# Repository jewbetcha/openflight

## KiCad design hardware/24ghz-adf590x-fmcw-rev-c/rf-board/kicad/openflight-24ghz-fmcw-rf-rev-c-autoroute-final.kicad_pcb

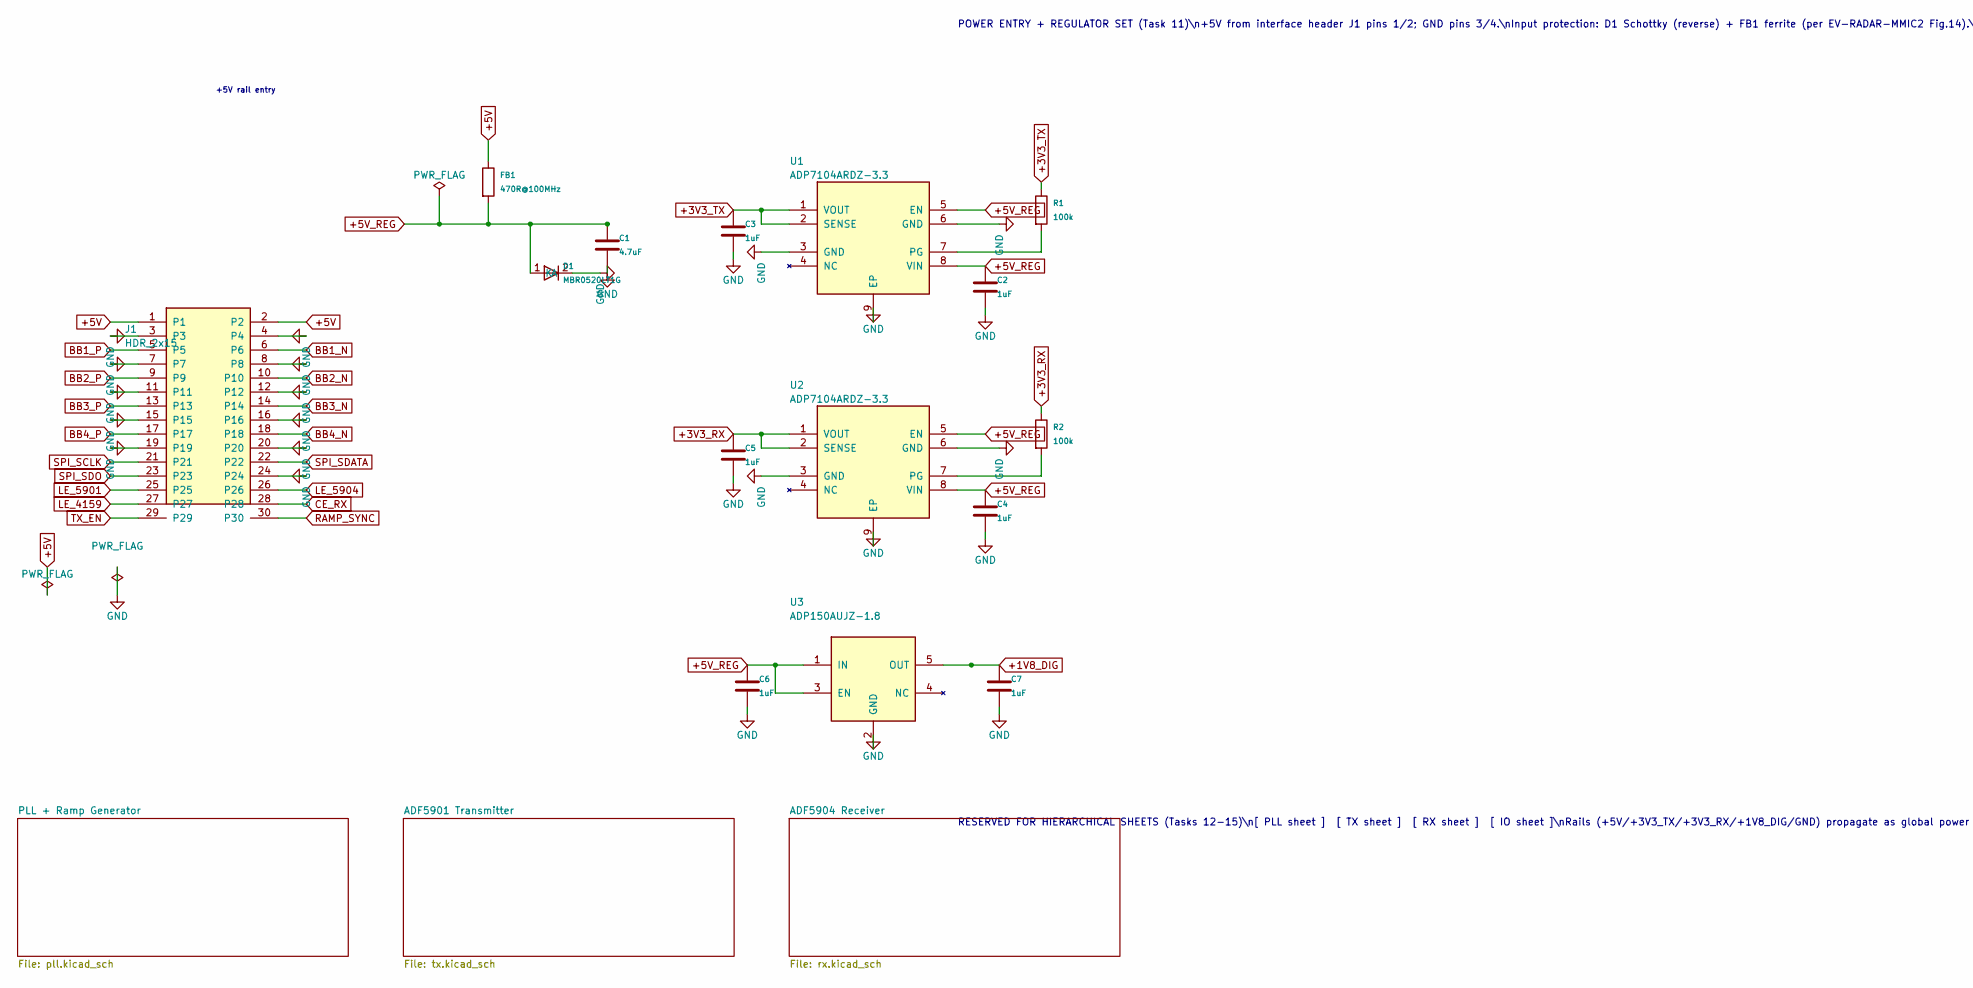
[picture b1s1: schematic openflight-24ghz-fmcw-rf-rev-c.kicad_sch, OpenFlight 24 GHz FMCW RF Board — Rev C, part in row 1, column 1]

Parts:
C1: 4.7uF; C_0603_1608Metric
C2, C3, C4, C5, C6, C7: 1uF; C_0603_1608Metric
D1: MBR0520LT1G; D_SOD-123; MPN MBR0520LT1G
FB1: 470R@100MHz; L_0603_1608Metric; MPN 742792642
J1: HDR_2x15; HDR_2x15_1.27MM_SMD; MPN FTSH-115-01-L-DV-K
R1, R2: 100k; R_0402_1005Metric
U1, U2: ADP7104ARDZ-3.3; ADP7104_SOIC8_EP; MPN ADP7104ARDZ-3.3
U3: ADP150AUJZ-1.8; ADP150_TSOT23_5; MPN ADP150AUJZ-1.8

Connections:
+1V8_DIG: C7.1, U3.5 (OUT); also elsewhere on the board
+3V3_RX: C5.1, R2.1, U2.1 (VOUT), U2.2 (SENSE); also elsewhere on the board
+3V3_TX: C3.1, R1.1, U1.1 (VOUT), U1.2 (SENSE); also elsewhere on the board
+5V: FB1.1, J1.1, J1.2; also elsewhere on the board
+5V_REG: C1.1, C2.1, C4.1, C6.1, D1.1 (K), FB1.2, U1.5 (EN), U1.8 (VIN), U2.5 (EN), U2.8 (VIN), U3.1 (IN), U3.3 (EN)
CE_RX: J1.28; also elsewhere on the board
LE_4159: J1.27; also elsewhere on the board
LE_5901: J1.25; also elsewhere on the board
LE_5904: J1.26; also elsewhere on the board
unnamed: R1.2, U1.7 (PG)
unnamed: R2.2, U2.7 (PG)
RAMP_SYNC: J1.30; also elsewhere on the board
SPI_SCLK: J1.21; also elsewhere on the board
SPI_SDATA: J1.22; also elsewhere on the board
SPI_SDO: J1.23; also elsewhere on the board
TX_EN: J1.29; also elsewhere on the board

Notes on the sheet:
POWER ENTRY + REGULATOR SET (Task 11)\n+5V from interface header J1 pins 1/2; GND pins 3/4.\nInput protection: D1 Schottky (reverse) + FB1 ferrite (per EV-RADAR-MMIC2 Fig.14).\nU1 ADP7104-3.3 -> +3V3_TX (ADF5901). U2 ADP7104-3.3 -> +3V3_RX (ADF5904 + ADF4159 analog).\nU3 ADP150-1.8 -> +1V8_DIG (ADF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
RESERVED FOR HIERARCHICAL SHEETS (Tasks 12-15)\n[ PLL sheet ] [ TX sheet ] [ RX sheet ] [ IO sheet ]\nRails (+5V/+3V3_TX/+3V3_RX/+1V8_DIG/GND) propagate as global power symbols;\nsignals cross via hierarchical pins added by those tasks.
+5V rail entry

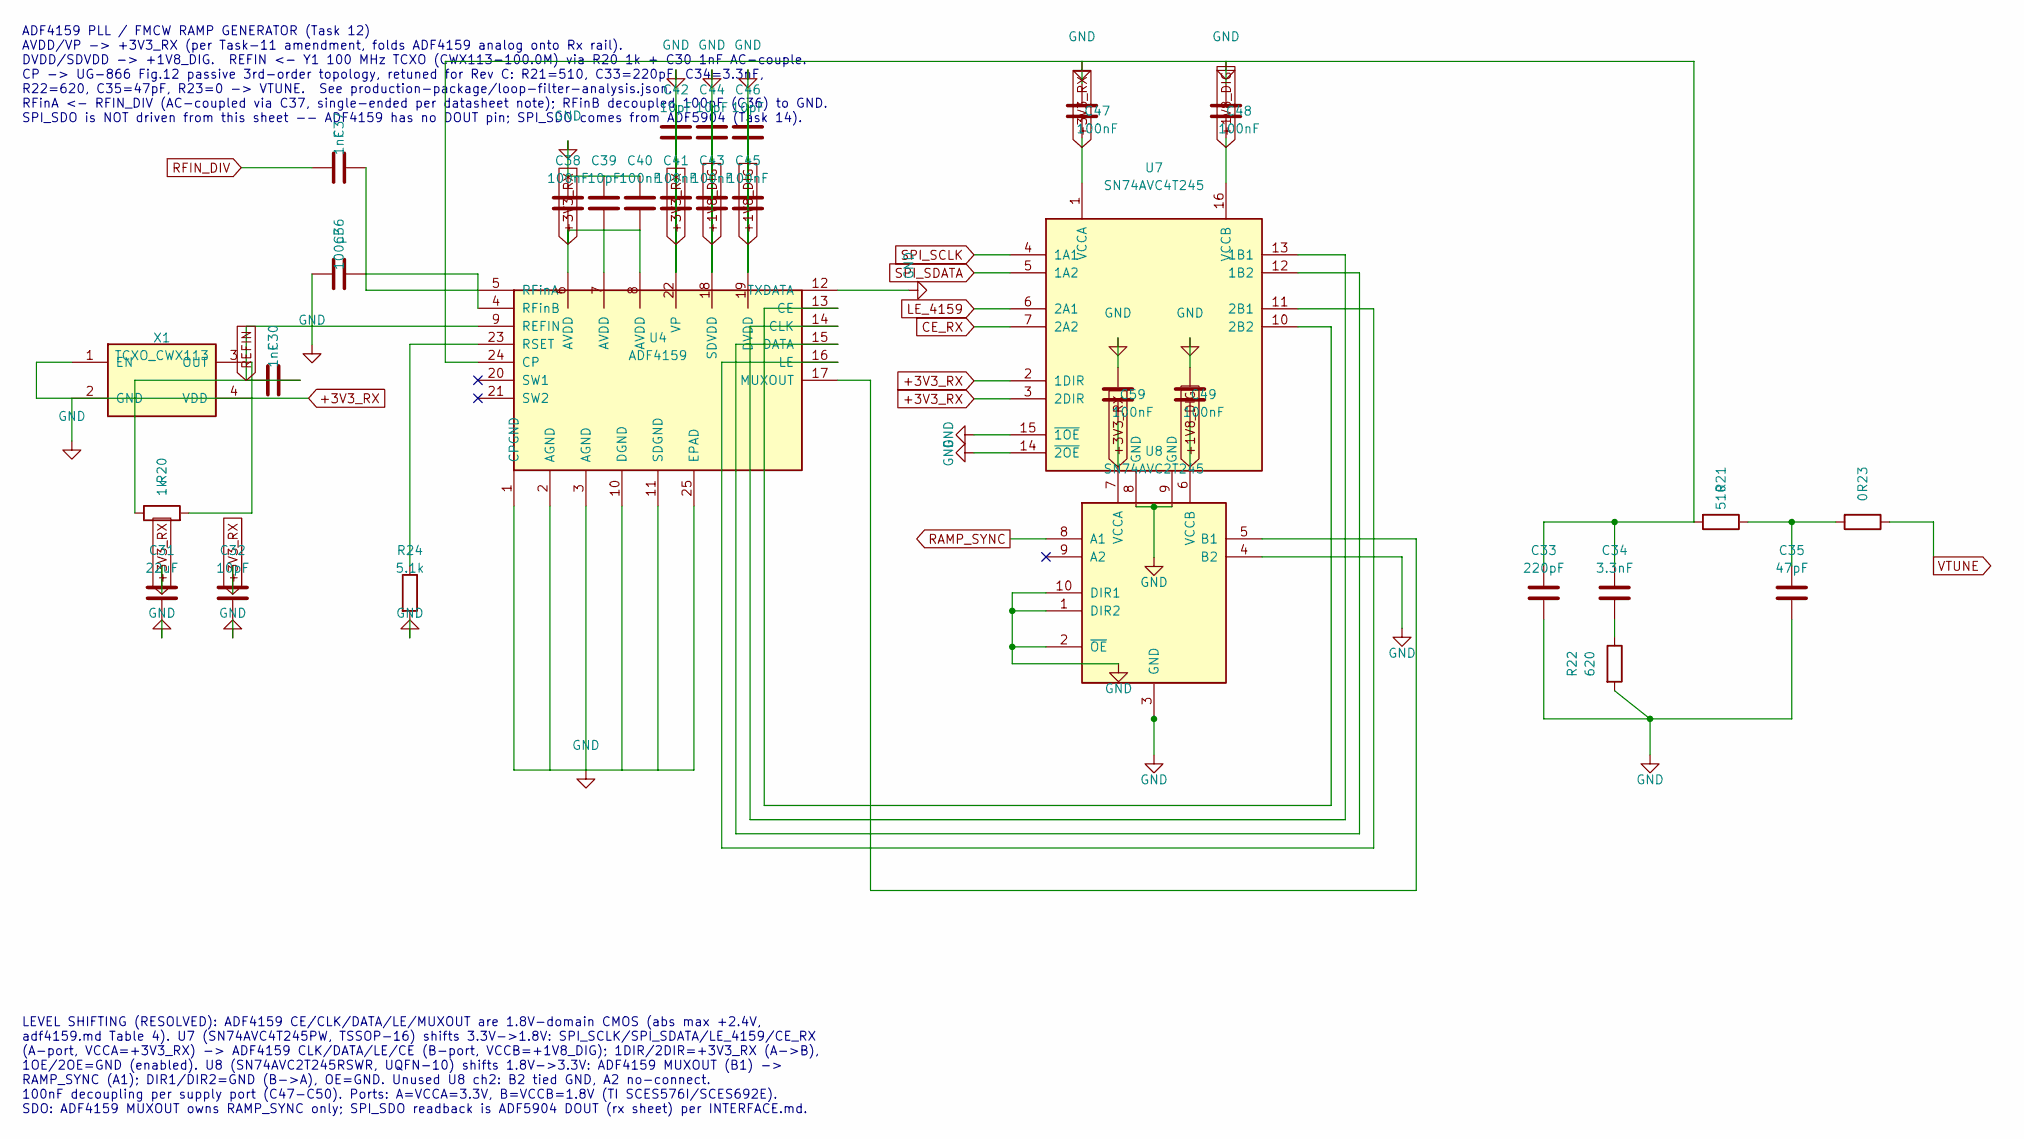
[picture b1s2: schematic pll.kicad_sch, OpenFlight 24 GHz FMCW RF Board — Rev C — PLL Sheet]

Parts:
C30, C37: 1nF; C_0402_1005Metric
C31: 22uF; C_0805_2012Metric
C32, C39, C42, C44, C46: 10pF; C_0402_1005Metric
C33: 220pF; C_0402_1005Metric
C34: 3.3nF; C_0402_1005Metric
C35: 47pF; C_0402_1005Metric
C36: 100pF; C_0402_1005Metric
C38, C40, C41, C43, C45, C47, C48, C49, C59: 100nF; C_0402_1005Metric
R20: 1k; R_0402_1005Metric
R21: 510; R_0402_1005Metric
R22: 620; R_0402_1005Metric
R23: 0; R_0402_1005Metric
R24: 5.1k; R_0402_1005Metric
U4: ADF4159; ADF4159_LFCSP24; MPN ADF4159CCPZ
U7: SN74AVC4T245; TSSOP-16_4.4x5mm_P0.65mm; MPN SN74AVC4T245PW
U8: SN74AVC2T245; Texas_RSW0010A_UQFN-10_1.4x1.8mm_P0.4mm; MPN SN74AVC2T245RSWR
X1: TCXO_CWX113; TCXO_CWX113_SMD4; MPN CWX113-100.0M

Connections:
+1V8_DIG: C43.2, C44.2, C45.2, C46.2, C48.2, C49.2, U4.18 (SDVDD), U4.19 (DVDD), U7.16 (VCCB), U8.6 (VCCB); also elsewhere on the board
+3V3_RX: C31.1, C32.1, C38.2, C39.2, C40.2, C41.2, C42.2, C47.2, C59.2, U4.6 (AVDD), U4.7 (AVDD), U4.8 (AVDD), U4.22 (VP), U7.1 (VCCA), U7.2 (1DIR), U7.3 (2DIR), U8.7 (VCCA), X1.1 (EN), X1.4 (VDD); also elsewhere on the board
CE_RX: U7.7 (2A2); also elsewhere on the board
LE_4159: U7.6 (2A1); also elsewhere on the board
unnamed: C30.2, R20.1
unnamed: U4.13 (CE), U7.10 (2B2)
unnamed: U4.14 (CLK), U7.13 (1B1)
unnamed: U4.15 (DATA), U7.12 (1B2)
unnamed: U4.16 (LE), U7.11 (2B1)
unnamed: U4.17 (MUXOUT), U8.5 (B1)
unnamed: C37.2, U4.5 (RFinA)
unnamed: C36.2, U4.4 (RFinB)
unnamed: R24.1, U4.23 (RSET)
unnamed: R20.2, X1.3 (OUT)
RAMP_SYNC: U8.8 (A1); also elsewhere on the board
REFIN: C30.1, U4.9 (REFIN); also elsewhere on the board
RFIN_DIV: C37.1; also elsewhere on the board
SPI_SCLK: U7.4 (1A1); also elsewhere on the board
SPI_SDATA: U7.5 (1A2); also elsewhere on the board

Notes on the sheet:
ADF4159 PLL / FMCW RAMP GENERATOR (Task 12) AVDD/VP -> +3V3_RX (per Task-11 amendment, folds ADF4159 analog onto Rx rail). DVDD/SDVDD -> +1V8_DIG. REFIN <- Y1 100 MHz TCXO (CWX113-100.0M) via R20 1k + C30 1nF AC-couple. CP -> UG-866 Fig.12 passive 3rd-order topology, retuned for Rev C: R21=510, C33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
LEVEL SHIFTING (RESOLVED): ADF4159 CE/CLK/DATA/LE/MUXOUT are 1.8V-domain CMOS (abs max +2.4V, adf4159.md Table 4). U7 (SN74AVC4T245PW, TSSOP-16) shifts 3.3V->1.8V: SPI_SCLK/SPI_SDATA/LE_4159/CE_RX (A-port, VCCA=+3V3_RX) -> ADF4159 CLK/DATA/LE/CE (B-port, VCCB=+1V8_DIG); 1DIR/2DIR=+3V3_RX (A->B), 1O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

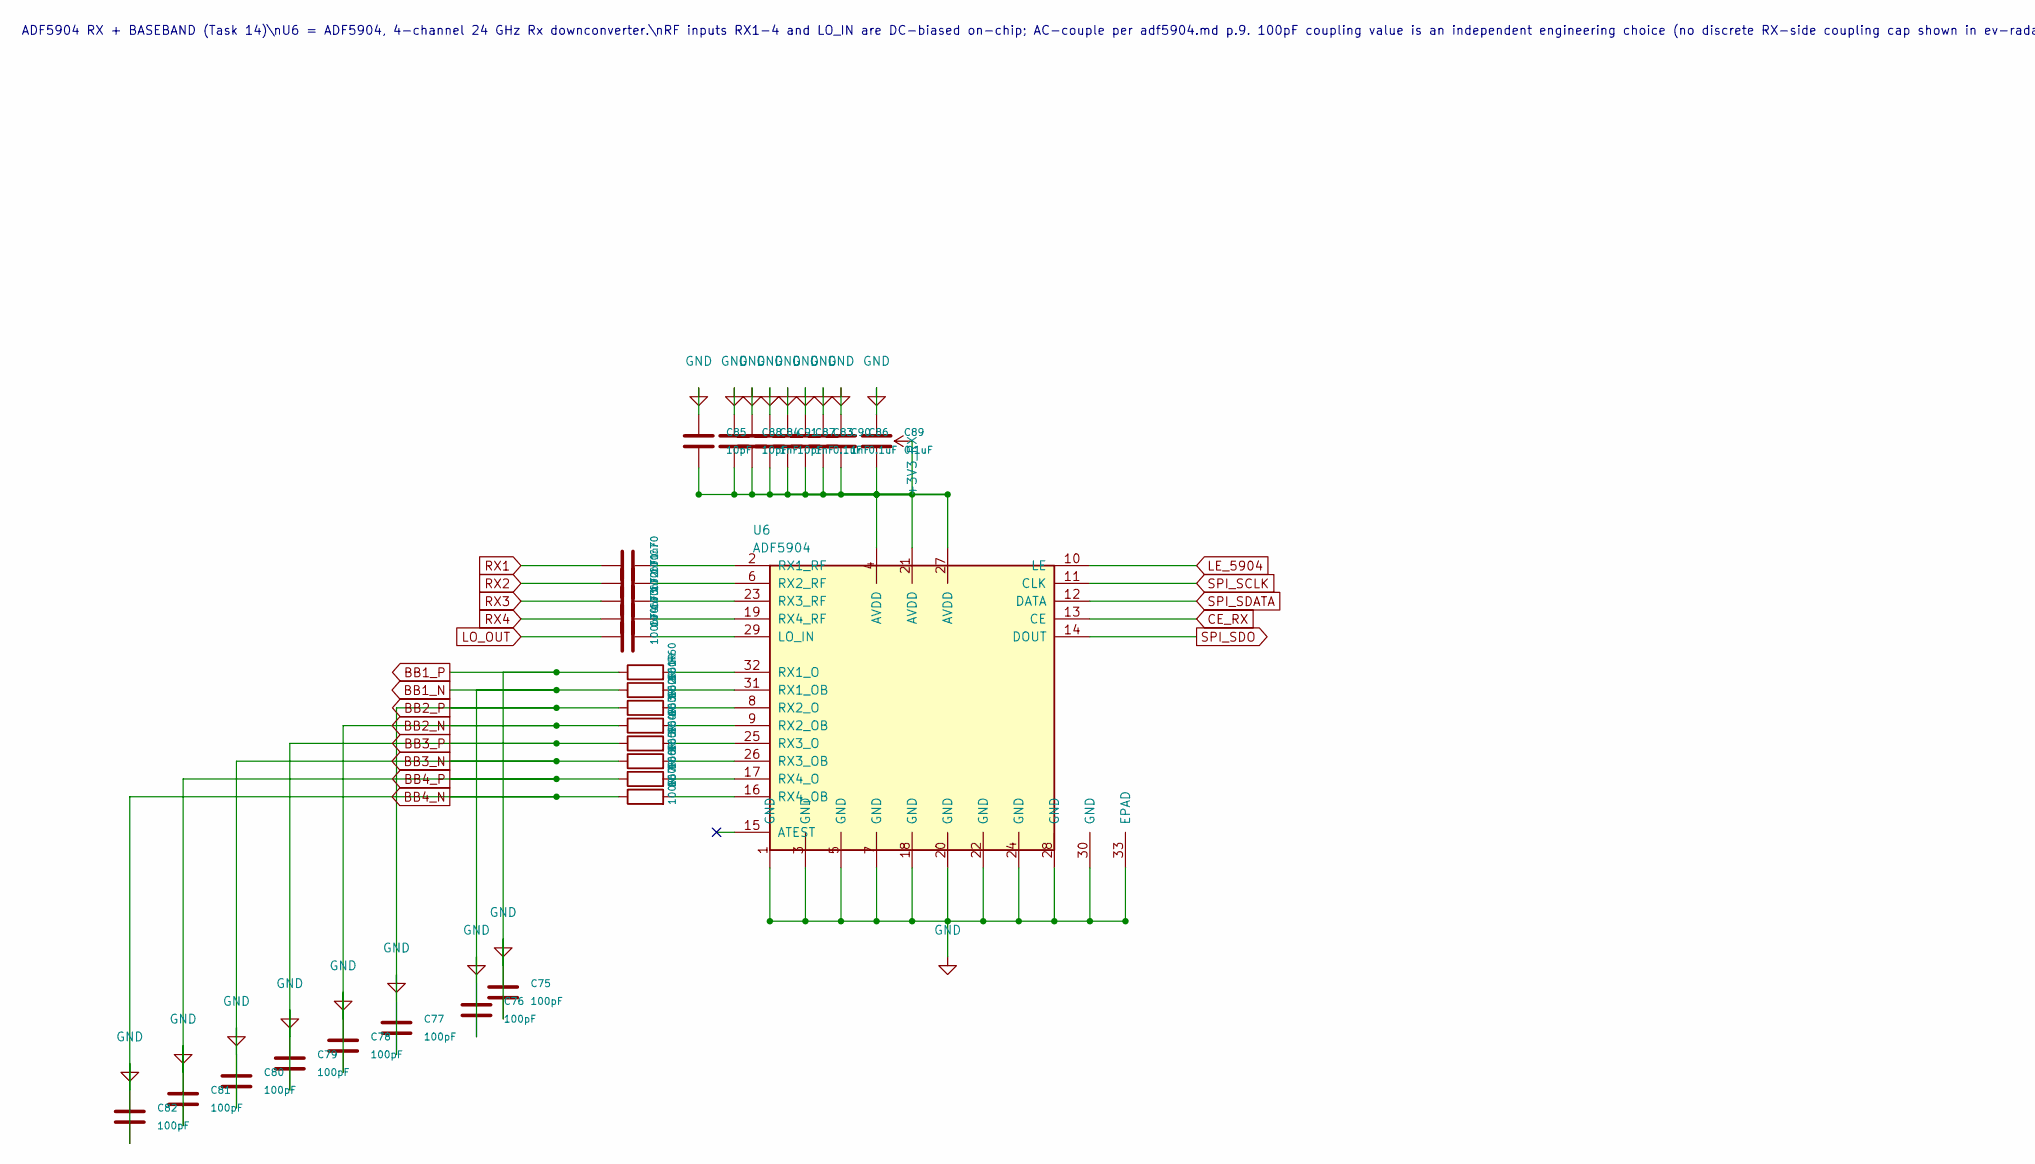
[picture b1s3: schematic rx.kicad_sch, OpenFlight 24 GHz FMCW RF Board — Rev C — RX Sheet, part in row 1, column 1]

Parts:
C70, C71, C72, C73, C74: 100nF; C_0402_1005Metric; MPN 550L104KTT
C75, C76, C77, C78, C79, C80, C81, C82: 100pF; C_0402_1005Metric
C83, C86, C89: 0.1uF; C_0402_1005Metric
C84, C87, C90: 1nF; C_0402_1005Metric
C85, C88, C91: 10pF; C_0402_1005Metric
R60, R61, R62, R63, R64, R65, R66, R67: 100R; R_0402_1005Metric
U6: ADF5904; ADF5904_LFCSP32; MPN ADF5904WCCPZ

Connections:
+3V3_RX: C83.2, C84.2, C85.2, C86.2, C87.2, C88.2, C89.2, C90.2, C91.2, U6.4 (AVDD), U6.21 (AVDD), U6.27 (AVDD); also elsewhere on the board
CE_RX: U6.13 (CE); also elsewhere on the board
LE_5904: U6.10 (LE); also elsewhere on the board
LO_OUT: C74.1; also elsewhere on the board
unnamed: C74.2, U6.29 (LO_IN)
unnamed: R60.2, U6.32 (RX1_O)
unnamed: R61.2, U6.31 (RX1_OB)
unnamed: C70.2, U6.2 (RX1_RF)
unnamed: R62.2, U6.8 (RX2_O)
unnamed: R63.2, U6.9 (RX2_OB)
unnamed: C71.2, U6.6 (RX2_RF)
unnamed: R64.2, U6.25 (RX3_O)
unnamed: R65.2, U6.26 (RX3_OB)
unnamed: C72.2, U6.23 (RX3_RF)
unnamed: R66.2, U6.17 (RX4_O)
unnamed: R67.2, U6.16 (RX4_OB)
unnamed: C73.2, U6.19 (RX4_RF)
RX1: C70.1; also elsewhere on the board
RX2: C71.1; also elsewhere on the board
RX3: C72.1; also elsewhere on the board
RX4: C73.1; also elsewhere on the board
SPI_SCLK: U6.11 (CLK); also elsewhere on the board
SPI_SDATA: U6.12 (DATA); also elsewhere on the board
SPI_SDO: U6.14 (DOUT); also elsewhere on the board

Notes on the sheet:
ADF5904 RX + BASEBAND (Task 14)\nU6 = ADF5904, 4-channel 24 GHz Rx downconverter.\nRF inputs RX1-4 and LO_IN are DC-biased on-chip; AC-couple per adf5904.md p.9. 100pF coupling value is an independent engineering choice (no discrete RX-side coupling cap shown in ev-radar-mmic2.md; Fig.23 there cove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

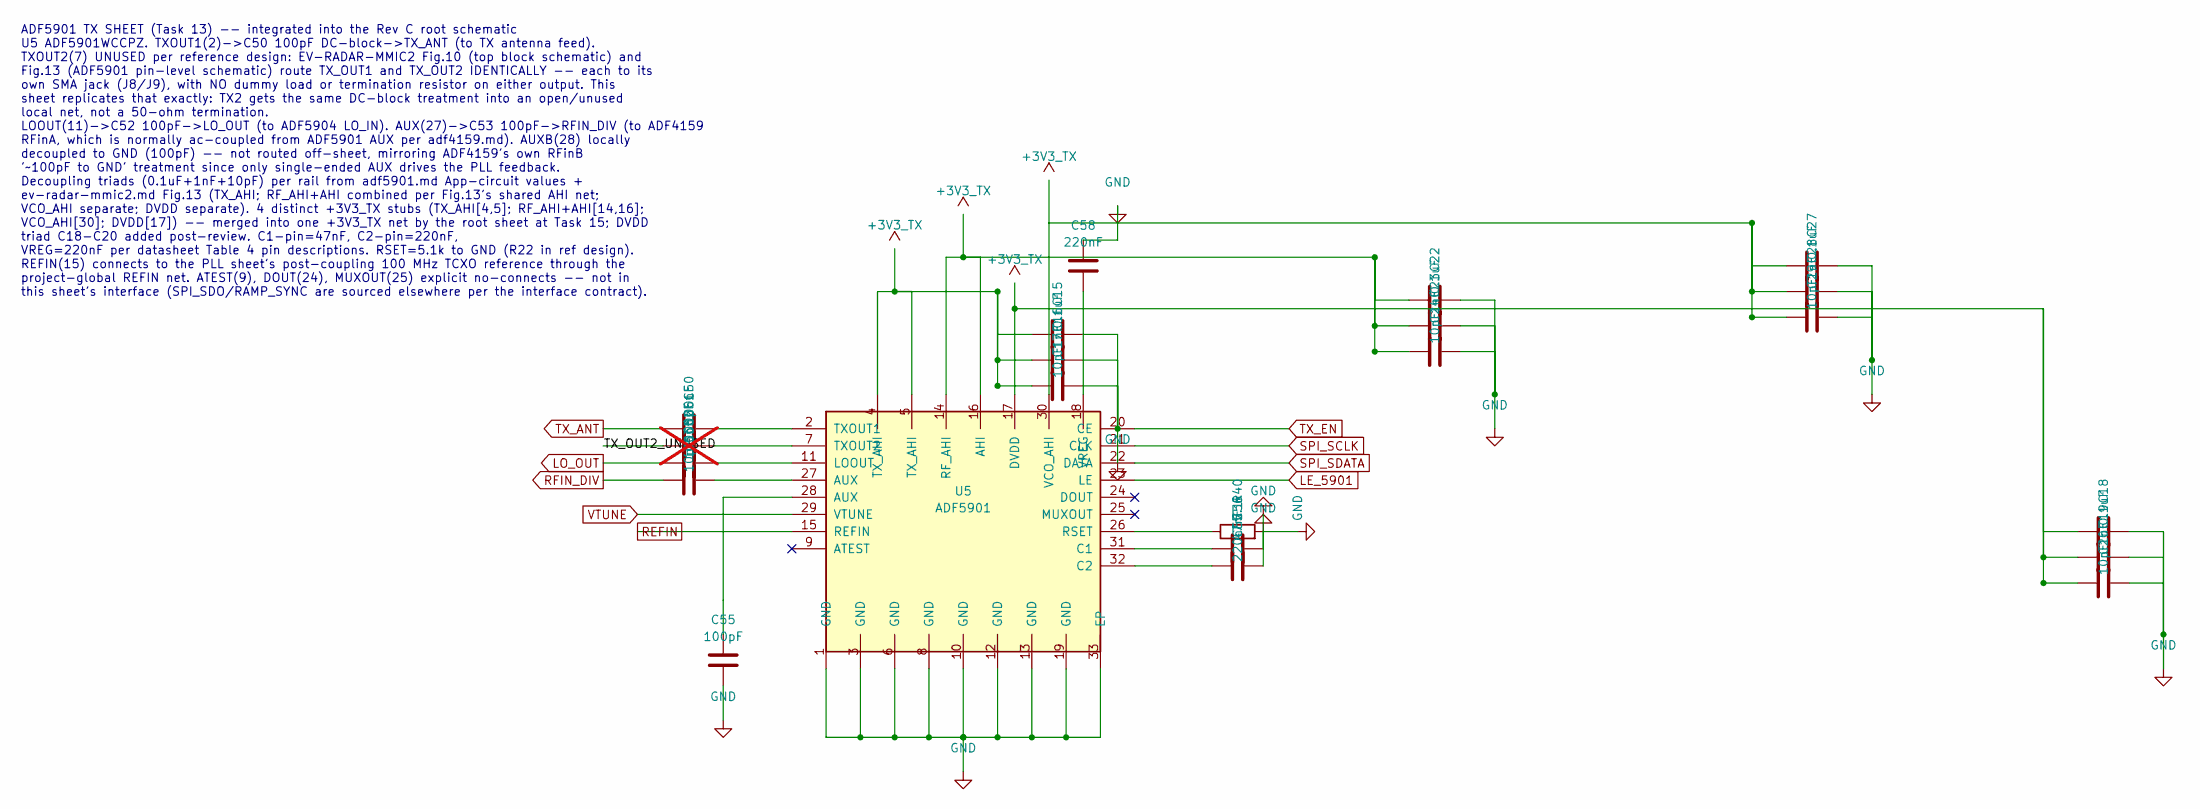
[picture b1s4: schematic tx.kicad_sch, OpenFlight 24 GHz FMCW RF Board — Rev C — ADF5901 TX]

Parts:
C15, C18, C22, C27: 0.1uF; C_0402_1005Metric
C16, C19, C23, C28: 1nF; C_0402_1005Metric
C17, C20, C24, C29: 10pF; C_0402_1005Metric
C50, C52: 100nF; C_0402_1005Metric; MPN 550L104KTT
C51: 100pF; C_0402_1005Metric; not fitted
C53: 10pF; C_0201_0603Metric; MPN 0201ZK100FBSTR
C55: 100pF; C_0402_1005Metric
C56: 47nF; C_0402_1005Metric
C57, C58: 220nF; C_0402_1005Metric
R40: 5.1k; R_0402_1005Metric
U5: ADF5901; ADF5901_LFCSP32; MPN ADF5901WCCPZ

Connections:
+3V3_TX: C15.1, C16.1, C17.1, C18.1, C19.1, C20.1, C22.1, C23.1, C24.1, C27.1, C28.1, C29.1, U5.4 (TX_AHI), U5.5 (TX_AHI), U5.14 (RF_AHI), U5.16 (AHI), U5.17 (DVDD), U5.30 (VCO_AHI); also elsewhere on the board
/ADF5901 Transmitter/TX_OUT2_UNUSED: C51.1
LE_5901: U5.23 (LE); also elsewhere on the board
LO_OUT: C52.1; also elsewhere on the board
unnamed: C53.2, U5.27 (AUX)
unnamed: C55.1, U5.28 (AUX)
unnamed: C56.1, U5.31 (C1)
unnamed: C57.1, U5.32 (C2)
unnamed: C52.2, U5.11 (LOOUT)
unnamed: R40.1, U5.26 (RSET)
unnamed: C50.2, U5.2 (TXOUT1)
unnamed: C51.2, U5.7 (TXOUT2)
unnamed: C58.2, U5.18 (VREG)
REFIN: U5.15 (REFIN); also elsewhere on the board
RFIN_DIV: C53.1; also elsewhere on the board
SPI_SCLK: U5.21 (CLK); also elsewhere on the board
SPI_SDATA: U5.22 (DATA); also elsewhere on the board
TX_ANT: C50.1; also elsewhere on the board
TX_EN: U5.20 (CE); also elsewhere on the board

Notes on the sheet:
ADF5901 TX SHEET (Task 13) -- integrated into the Rev C root schematic U5 ADF5901WCCPZ. TXOUT1(2)->C50 100pF DC-block->TX_ANT (to TX antenna feed). TXOUT2(7) UNUSED per reference design: EV-RADAR-MMIC2 Fig.10 (top block schematic) and Fig.13 (ADF5901 pin-level schematic) route TX_OUT1 and TX_OUT2 I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

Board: 4 copper layers, 114 parts (0 on the bottom side), 69 nets, no tracks yet.

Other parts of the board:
ANT_RX1: RX1; RX_SUBARRAY_2X2
ANT_RX2: RX2; RX_SUBARRAY_2X2
ANT_RX3: RX3; RX_SUBARRAY_2X2
ANT_RX4: RX4; RX_SUBARRAY_2X2
ANT_TX1: TX_ANT; TX_ARRAY_2X2
FID1, FID2, FID3: Fiducial; Fiducial_1mm_Mask2mm
H1, H2, H3, H4: M2.5; MountingHole_2.7mm
TP1: +5V; TestPoint_Pad_D1.0mm
TP2: +3V3_TX; TestPoint_Pad_D1.0mm
TP3: +3V3_RX; TestPoint_Pad_D1.0mm
TP4: +1V8_DIG; TestPoint_Pad_D1.0mm

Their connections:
+1V8_DIG: TP4.1; also elsewhere on the board
+3V3_RX: TP3.1; also elsewhere on the board
+3V3_TX: TP2.1; also elsewhere on the board
+5V: TP1.1; also elsewhere on the board
RX1: ANT_RX1.1; also elsewhere on the board
RX2: ANT_RX2.1; also elsewhere on the board
RX3: ANT_RX3.1; also elsewhere on the board
RX4: ANT_RX4.1; also elsewhere on the board
TX_ANT: ANT_TX1.1; also elsewhere on the board
